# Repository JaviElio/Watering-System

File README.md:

View this project on [CADLAB.io](https://cadlab.io/node/1000). 

# Watering-System
Watering system with Attiny85 and i2c moisture sensor.

**FEATURES:**

 - Measures soil moisture, light and temperature.
 - It waters only at night.
 - It doesn't water if temperature is below 4ºC.
 - It waters depending on a preset value and a hysteresis.

 - It takes measurements every hour, then microcontroller goes to deep sleep.
 - If it irrigates, then checks moisture again after five minutes.

**BILL OF MATERIALS:**

 - Valve: https://www.aliexpress.com/item/Free-shipping-Plastic-solenoid-valve-12VDC-for-drink-water-air-6-35mm-1-4-Quick-plug/1411672083.html?spm=2114.13010608.0.0.Ew7MCd
 
 - I2C Soil moisture sensor: https://www.tindie.com/products/miceuz/i2c-soil-moisture-sensor/?pt=full_prod_search
 
 - Enclosure: https://www.aliexpress.com/item/New-1-PC-Waterproof-115x90x55MM-Cover-Plastic-Electronic-Project-Box-Enclosure-Case-VE837-P0-3/32701644399.html?spm=2114.13010608.0.0.FBugqX
 
 - Attiny85
 - MAX663CPA
 - 2N7000
 - BS170

**PICTURES:**

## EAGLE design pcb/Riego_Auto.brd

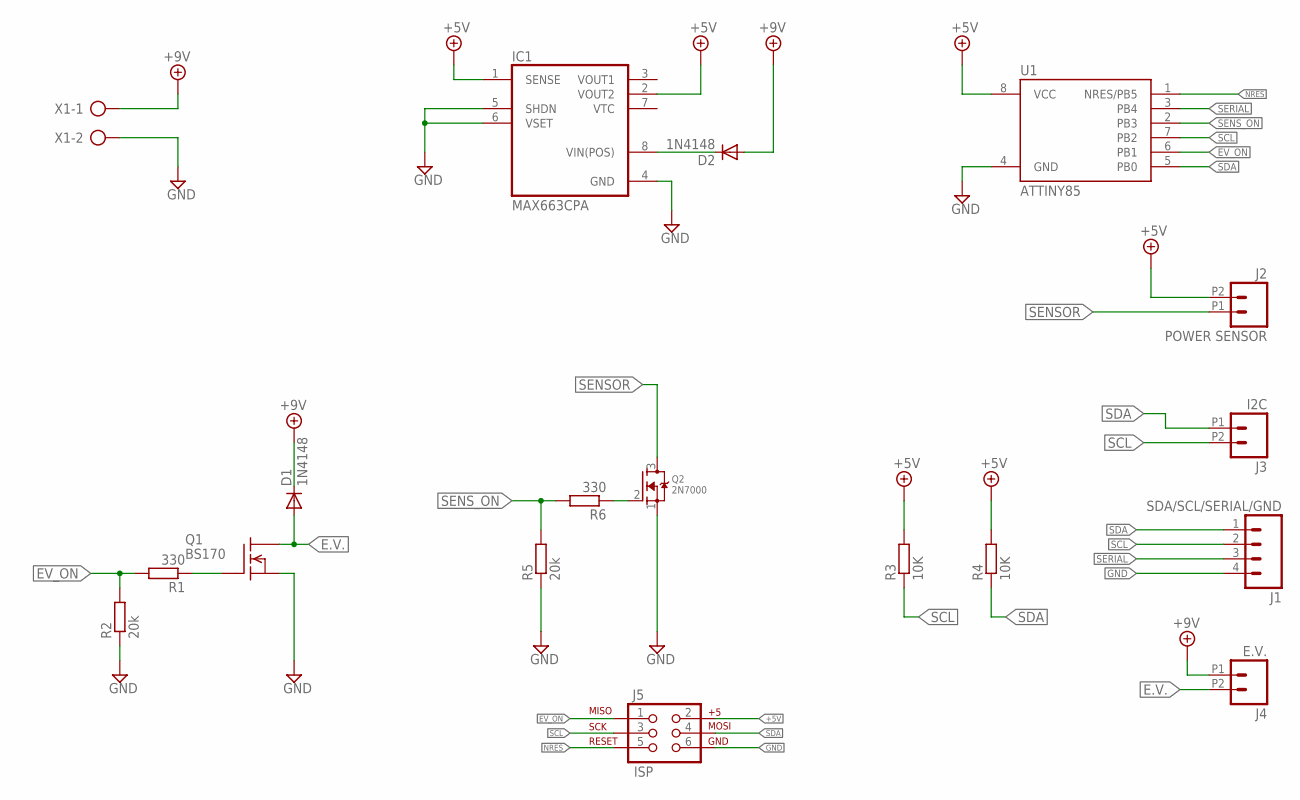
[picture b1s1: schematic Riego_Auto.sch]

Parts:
D1, D2: 1N4148; DO35-7
IC1: MAX663CPA; DIL08
J1: SDA/SCL/SERIAL/GND; 1X04
J2: POWER SENSOR; 1X02_2.54_SCREWTERM
J3: I2C; 1X02_2.54_SCREWTERM
J4: E.V.; 1X02_2.54_SCREWTERM
J5: ISP; 2X3
Q1: BS170; TO92-INLINE
Q2: 2N7000; TO92-INLINE
R1, R6: 330; 0204/7
R2, R5: 20k; 0204/7
R3, R4: 10K; 0204/7
U1: ATTINY85; DIL08
X1: AK500/2

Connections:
+5V: IC1.1 (SENSE), IC1.2 (VOUT2), J2.P2 (2), J5.2, R3.2, R4.2, U1.8 (VCC)
+12V: D1.C, D2.A, J4.P1 (1), X1.1
E.V.: D1.A, J4.P2 (2), Q1.1 (D)
EV_ON: J5.1, R1.2, R2.2, U1.6 (PB1)
GND: IC1.4 (GND), IC1.5 (SHDN), IC1.6 (VSET), J1.4, J5.6, Q1.3 (S), Q2.1 (S), R2.1, R5.1, U1.4 (GND), X1.2
unnamed: Q1.2 (G), R1.1
unnamed: D2.C, IC1.8 (VIN(POS))
unnamed: Q2.2 (G), R6.1
NRES: J5.5, U1.1 (NRES/PB5)
SCL: J1.2, J3.P2 (2), J5.3, R3.1, U1.7 (PB2)
SDA: J1.1, J3.P1 (1), J5.4, R4.1, U1.5 (PB0)
SENSOR: J2.P1 (1), Q2.3 (D)
SENS_ON: R5.2, R6.2, U1.2 (PB3)
SERIAL: J1.3, U1.3 (PB4)

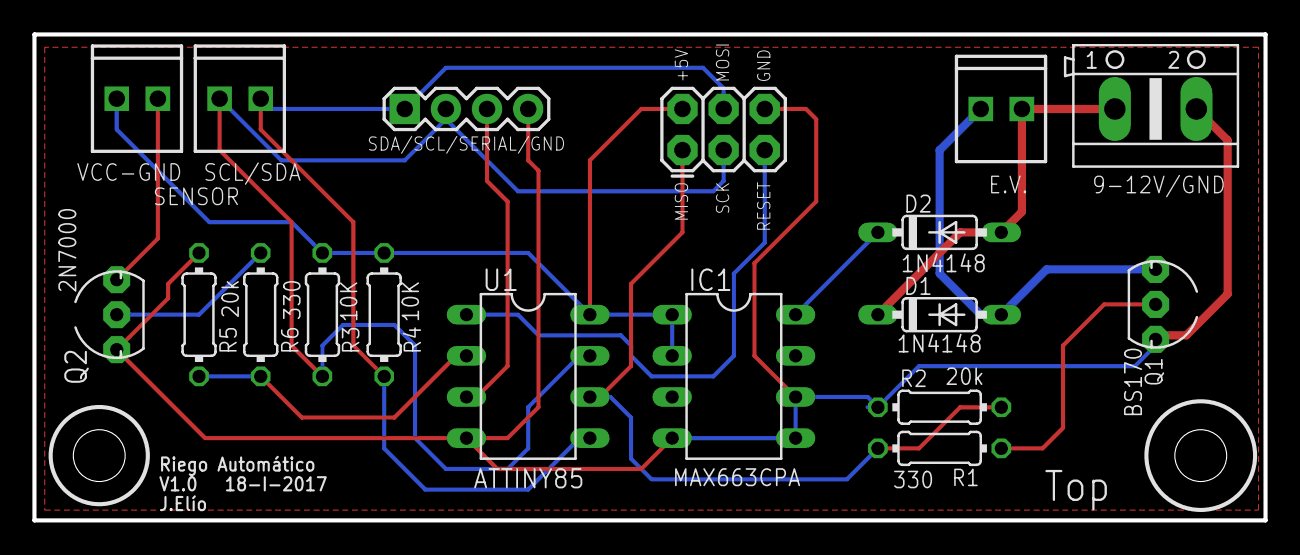
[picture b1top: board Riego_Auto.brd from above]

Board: 2 copper layers, 76.0 x 30.0 mm, 18 parts (0 on the bottom side), 14 nets.

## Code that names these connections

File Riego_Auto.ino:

/*
  Proyecto: Riego Automatico V1.0    27-12-2016
  JEC
*/

#include <TinyWireM.h>                      // Libreria para comunicacion i2c Attiny85
#include <SoftwareSerial.h>                 // Libreria para crear puerto serie por software
#include <I2CSoilMoistureSensor.h>          // Libreria para comunicación i2c con sensor humedad

#include <avr/sleep.h>                      // Libreria para gestion de energia
#include <avr/wdt.h>                        // Libreria para uso del watchdog
#include <avr/interrupt.h>                  // Libreria para interrupciones

#define SENSOR PB3                          // Activacion sensor humedad
#define E_VALVE PB1                         // Activacion electrovalvula


// Crear un puerto serie
SoftwareSerial puertoSerie(-1, 4);

// Crear objeto sensor
I2CSoilMoistureSensor sensor;


// Variables
unsigned int nLight;                      // Valor de luz medido
unsigned int nLightMax = 30000;           // Valor de luz maximo para regar
unsigned int nTemp;                       // Valor de temperatura medido
unsigned int nTempMin  = 40;              // Valor de temperatura mínimo para regar
unsigned int nTempMed  = 80;              // Valor de temperatura "regar con luz"
unsigned int nMoisture;                   // Valor de humedad medido
unsigned int nMoistureMin = 350;          // Valor de humedad mínimo para regar
unsigned int nMoistureMax = 450;          // Valor de humedad máximo para regar

unsigned int nState = 0;                  // indice "Switch"
bool bOldValvula = 0;                     // Estado anterior de la válvula
unsigned int nRepeticiones = 0;           // Veces que se ha regado
unsigned int nRepeticionesMax = 5;        // Repeticiones máximas


void setup() {

  configurePins();                   // Configurar pines

  TinyWireM.begin();                 // Iniciar comunicacion i2c
  puertoSerie.begin(9600);           // Iniciar puerto serie

  setupPowerSaving();                // Configurar ahorro de energia

}


void loop() {

  switch (nState) {

    case 0: // Encender sensor

      puertoSerie.println("Encendiendo sensor (case 0)");
      digitalWrite(SENSOR, true);
      delay(2000);
      sensor.begin();                                         // Iniciar sensor
      delay(2000);

      nState = 10;
      break;

    case 10:  // Medir luz

      puertoSerie.print("Midiendo luz (case 10):   ");
      nLight = sensor.getLight(true);
      puertoSerie.println(nLight);

      puertoSerie.print("Midiendo temperatura (case 10):   ");
      nTemp = sensor.getTemperature();
      puertoSerie.println(nTemp);


      // Si "oscuro" y temperatura mayor que 4º se riega
      if ((nLight > nLightMax) && nTemp > nTempMed) {
        nState = 20;
      }

      // Si "luz" y temperatura entre 4ºC y 8ºC se riega
      else if ((nLight < nLightMax) && (nTemp > nTempMin && nTemp <= nTempMed)) {
        nState = 20;
      }

      else {
        // No regar -> sleep
        nRepeticiones = 0;
        bOldValvula = false;
        nState = 200;
      }

      break;

    case 20: // Leer humedad

      puertoSerie.print("Midiendo humedad (case 20):   ");
      nMoisture = sensor.getCapacitance();
      puertoSerie.println(nMoisture);


      if ((nMoisture < nMoistureMin) || (nMoisture < nMoistureMax) && bOldValvula) {

        nRepeticiones++;

        if (nRepeticiones > nRepeticionesMax) {
          puertoSerie.println("Max repeticiones alcanzadas!!!!");
          nRepeticiones = 0;
          bOldValvula = false;
          nState = 200;
        }
        else {
          bOldValvula = true;
          nState = 30;
        }
      }

      if ((nMoisture > nMoistureMax) || (nMoisture > nMoistureMin) && !bOldValvula) {

        nRepeticiones = 0;
        bOldValvula = false;
        nState = 200;
      }

      break;

    case 30:  // Regar

      puertoSerie.println("Regando (case 30)");
      digitalWrite(SENSOR, false);    // Apagar sensor
      digitalWrite(E_VALVE, true);    // Encender electroValvula
      delay(5000);
      digitalWrite(E_VALVE, false);   // Apagar electrovalvula

      nState = 100;
      break;


    case 100:   // Sleep "corto"

      puertoSerie.println("Sleep corto (case100)");

      digitalWrite(SENSOR, false);    // Apagar sensor
      sleep(1);                       // dormir 1x8segundos = 8 segundos

      nState = 0;
      break;

    case 200:   // Sleep "largo"

      puertoSerie.println("Sleep largo (case200)");

      digitalWrite(SENSOR, false);    // Apagar sensor
      sleep(2);                       // dormir 2x8segundo = 16 segundos

      nState = 0;
      break;


    default: nState = 0;

  }

}


void setupWatchdog() {
  cli();
  // Set watchdog timer in interrupt mode
  // allow changes, disable reset
  WDTCR = bit (WDCE) | bit (WDE);
  // set interrupt mode and an interval
  WDTCR = bit (WDIE) | bit (WDP3) | bit (WDP0);    // set WDIE, and 8 seconds delay
  sei(); // Enable global interrupts
}


void sleep(int times) {

  setupWatchdog();                                // Configurar y activar WDT

  for (int i = 1; i <= times; i++) {

    cli();                                       // Deshabilitar las interrupciones por si acaso
    sleep_enable();                              // Habilitar sleep


    //    sleep_bod_disable();                       // Deshabilitar BOD durante sleep
    //    MCUCR |= _BV(BODS) | _BV(BODSE);           //disable brownout detection during sleep
    //    MCUCR &=~ _BV(BODSE);

    sei();                                       // Habilitar interrupciones
    sleep_cpu();                                 // Dormir....
    sleep_disable();                             // Deshabilitar sleep una vez despierto.

  }

  wdt_disable();                                // Deshabilitar WDT para no más interrupciones
}


void setupPowerSaving() {

  // Desconectar ADC
  ADCSRA &= ~(1 << ADEN);

  // Modo "sleep"
  set_sleep_mode(SLEEP_MODE_PWR_DOWN);

  // Desconectar modulos Timer1, adc
  // PRR=B1001;
}

void configurePins() {

  //pinMode(PB0, OUTPUT);               // i2c SDA
  pinMode(PB1, OUTPUT);                 // E_VALVE
  // pinMode(PB2, OUTPUT);              // i2c SCL
  pinMode(PB3, OUTPUT);                 // SENSOR
  //pinMode(PB4, OUTPUT);               // Tx
  //pinMode(PB5, OUTPUT);               // Rx

  //digitalWrite(PB0, false);           // i2c SDA
  digitalWrite(PB1, false);             // E_VALVE
  //digitalWrite(PB2, false);           // i2c SCL
  digitalWrite(PB3, false);             // SENSOR
  //digitalWrite(PB4, false);           // Tx
  //digitalWrite(PB5, false);           // Rx

}

ISR(WDT_vect) {

  // Nada

}

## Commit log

2017-02-08 V1.0
2017-02-08 Rename Riego_Auto_V1.0.ino to Riego_Auto.ino
2017-02-08 Rename Riego_Auto_V1.0.brd to Riego_Auto.brd
2017-02-08 Rename Riego_Auto_V1.0.sch to Riego_Auto.sch
2017-02-17 Update README.md
    BOM added
2017-02-17 Bypass Capacitors Added
    Attiny bypass capcitor added
    Moisture sensor bypass capacitor added
2017-02-18 Update README.md
    Enclosure link added
2017-02-28 Rename Riego_Auto.brd to pcb/Riego_Auto.brd
2017-02-28 Rename Riego_Auto.sch to pcb/Riego_Auto.sch
2017-02-28 Rename Riego_Auto_V1.0.sch to pcb/Riego_Auto_V1.0.sch
2017-02-28 Rename Riego_Auto_V1.0.brd to pcb/Riego_Auto_V1.0.brd
2017-02-28 Rename Riego_Auto.ino to src/Riego_Auto.ino
2017-03-21 Adding some variables for sleep delays
2017-03-21 File moved to another folder
2017-03-21 Some comments translated
2017-03-22 Some comments and variables translated
2017-03-22 resolution reduced
2017-03-22 one Watering case deleted
2017-03-25 Comment changed
2017-04-08 Fix wrong variable
2017-05-13 Watering time reduced
2018-05-08 Backlink to CADLAB.io has been added.

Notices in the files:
parts and their libraries:
SparkFun-Connectors: Licensing: Creative Commons ShareAlike 4.0 International - https://creativecommons.org/licenses/by-sa/4.0
